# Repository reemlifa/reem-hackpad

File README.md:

# hackpad
reems first hackpad

BOM
- 8 diodes
- 8 cherry mx switches
- 1 rotary encoder
- 1 XIAO RP2040 DIP

What it does
* Key Presses: Pressing the switches sends Function Keys (F1-F11) and the letter 'A' to the computer. This is defined in the keymap.
* Encoder Rotation:
    * Turning it clockwise sends a Volume Up command.
    * Turning it counter-clockwise sends a Volume Down command.
* Encoder Click: Pressing the encoder's button sends a Mute command.

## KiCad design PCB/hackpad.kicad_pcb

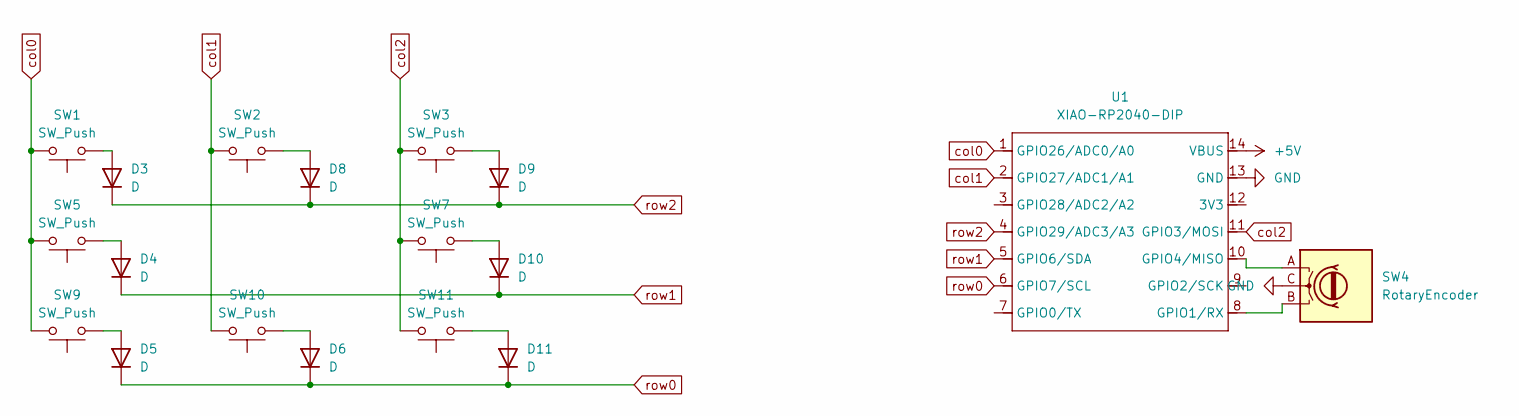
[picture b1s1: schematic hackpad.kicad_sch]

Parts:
D3, D4, D5, D6, D8, D9, D10, D11: D; D_DO-201AE_P3.81mm_Vertical_KathodeUp
SW1, SW2, SW3, SW5, SW7, SW9, SW10, SW11: SW_Push; SW_Cherry_MX_1.00u_PCB
SW4: RotaryEncoder; RotaryEncoder_Alps_EC11E_Vertical_H20mm_CircularMountingHol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
U1: XIAO-RP2040-DIP

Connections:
+5V: U1.14 (VBUS)
GND: SW4.C, U1.13 (GND)
unnamed: D3.2 (A), SW1.1
unnamed: D4.2 (A), SW5.1
unnamed: D5.2 (A), SW9.1
unnamed: D6.2 (A), SW10.1
unnamed: D8.2 (A), SW2.1
unnamed: D9.2 (A), SW3.1
unnamed: D10.2 (A), SW7.1
unnamed: D11.2 (A), SW11.1
unnamed: SW4.B, U1.8 (GPIO1/RX)
unnamed: SW4.A, U1.10 (GPIO4/MISO)
col0: SW1.2, SW5.2, SW9.2, U1.1 (GPIO26/ADC0/A0)
col1: SW2.2, SW10.2, U1.2 (GPIO27/ADC1/A1)
col2: SW3.2, SW7.2, SW11.2, U1.11 (GPIO3/MOSI)
row0: D5.1 (K), D6.1 (K), D11.1 (K), U1.6 (GPIO7/SCL)
row1: D4.1 (K), D10.1 (K), U1.5 (GPIO6/SDA)
row2: D3.1 (K), D8.1 (K), D9.1 (K), U1.4 (GPIO29/ADC3/A3)

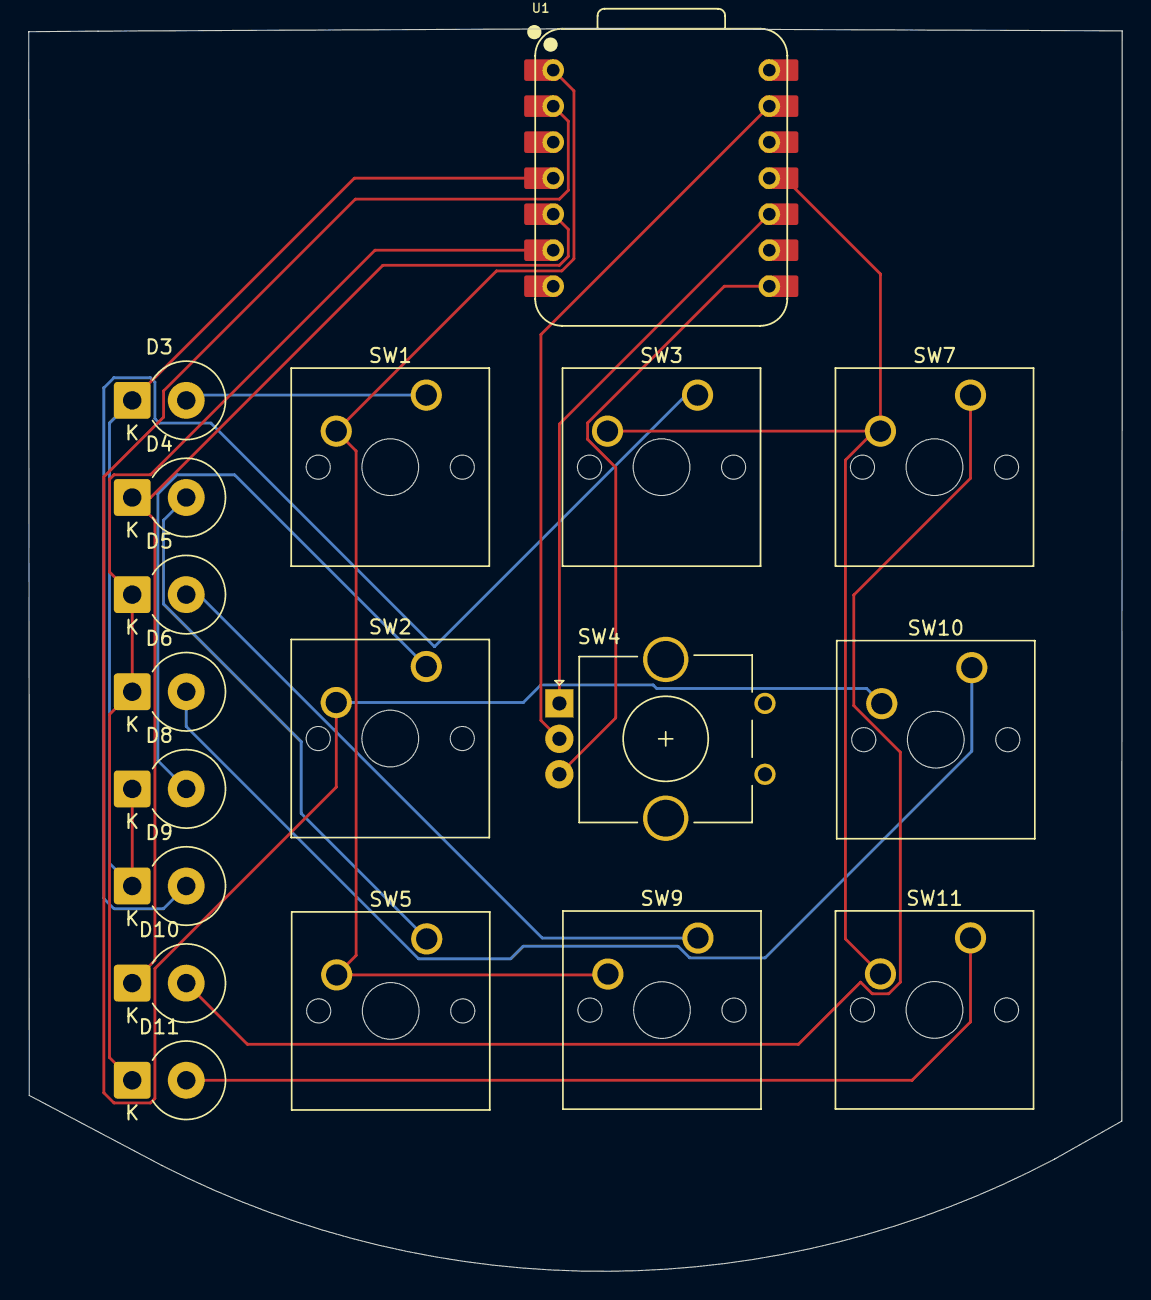
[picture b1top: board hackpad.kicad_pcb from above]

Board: 2 copper layers, 77.1 x 87.6 mm, 18 parts (0 on the bottom side), 17 nets.

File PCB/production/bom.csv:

Designator,Footprint,Quantity,Value,LCSC Part #
"D10, D11, D3, D4, D5, D6, D8, D9",D_DO-201AE_P3.81mm_Vertical_KathodeUp,8,D,
"SW1, SW10, SW11, SW2, SW3, SW5, SW7, SW9",SW_Cherry_MX_1.00u_PCB,8,SW_Push,
SW4,RotaryEncoder_Alps_EC11E_Vertical_H20mm_CircularMountingHoles,1,RotaryEncoder,
U1,XIAO-RP2040-DIP,1,XIAO-RP2040-DIP,

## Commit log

2025-07-09 Just put like leo
2025-07-10 Cleaned up backups and updated project files
2025-07-10 fixed
